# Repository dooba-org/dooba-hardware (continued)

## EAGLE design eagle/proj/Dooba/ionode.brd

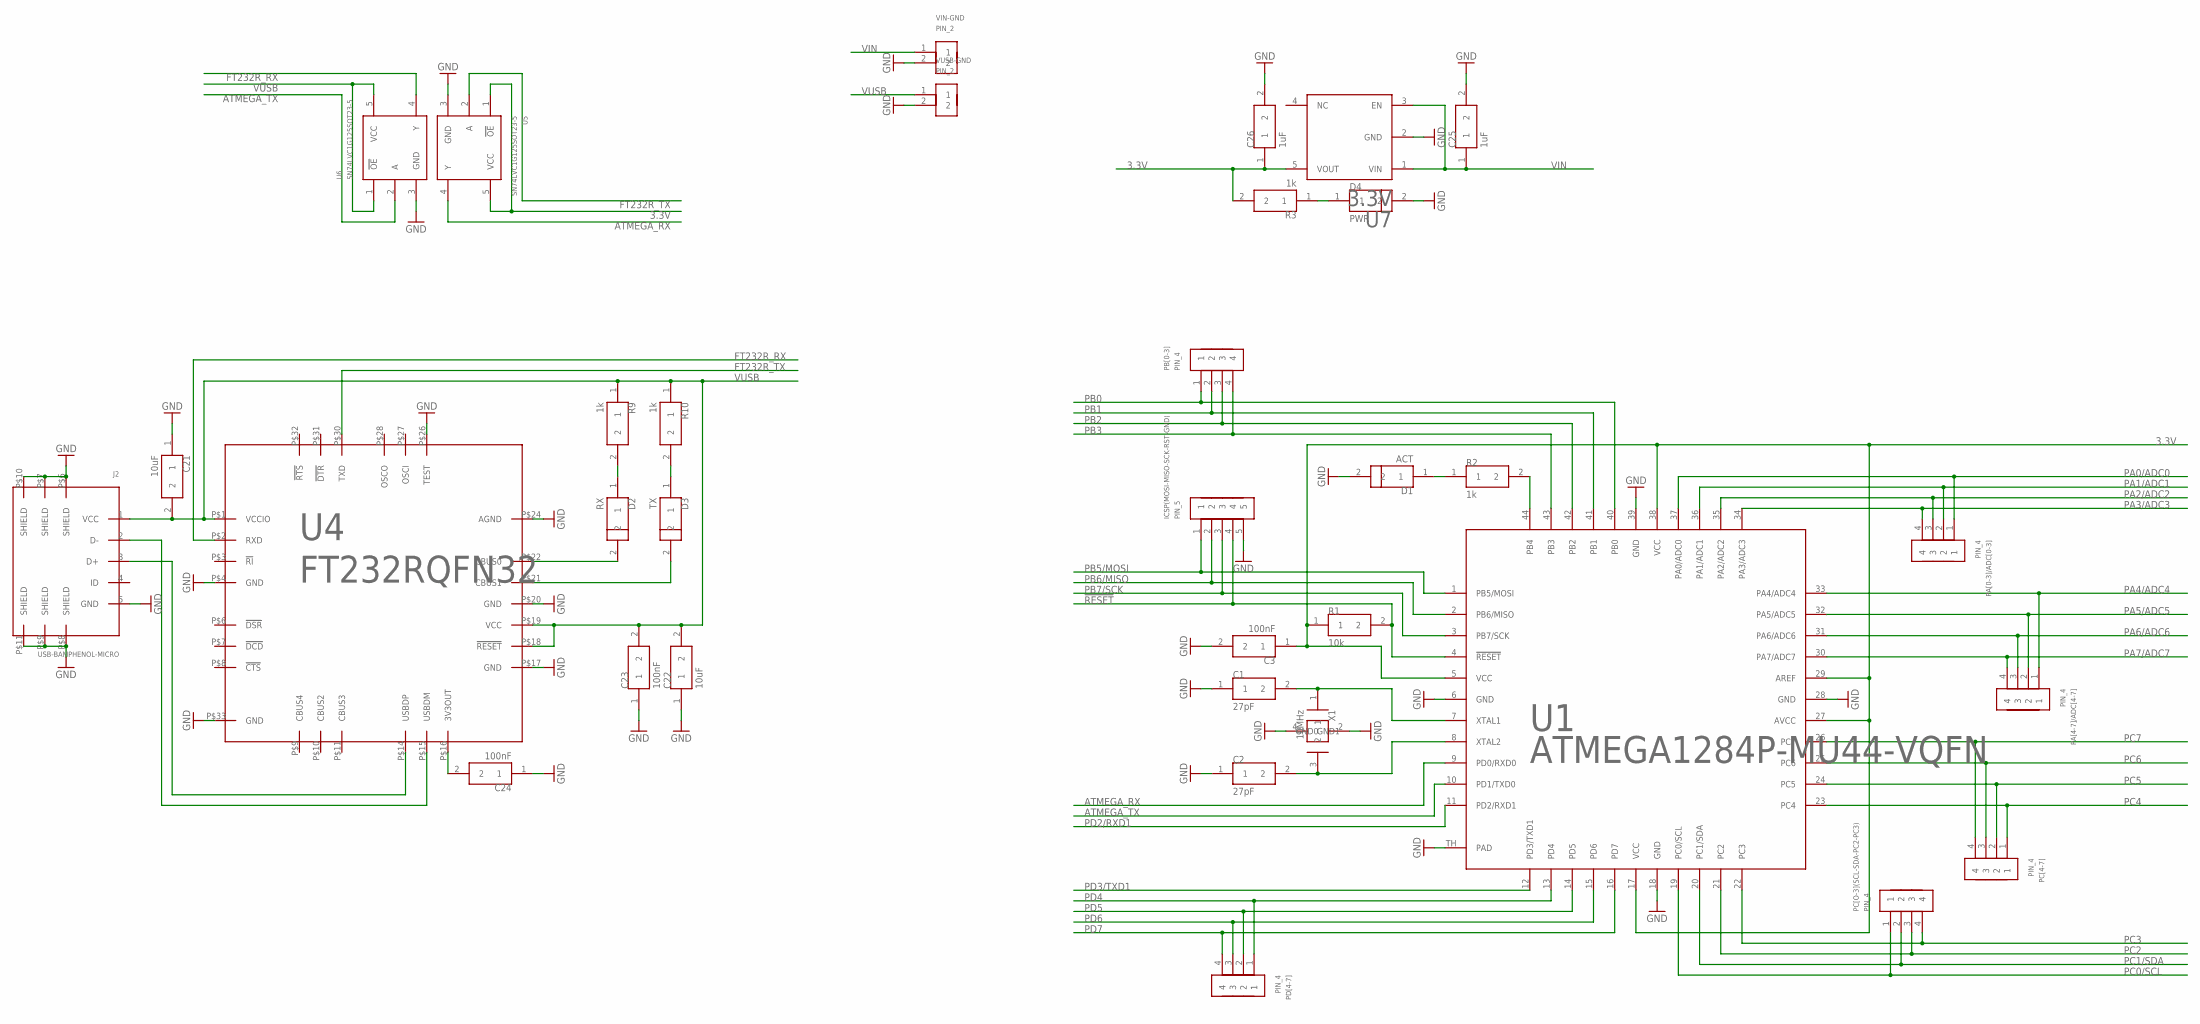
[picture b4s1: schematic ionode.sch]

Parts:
C1, C2: 27pF; 0805
C3, C23, C24: 100nF; 0805
C21, C22: 10uF; 0805
C25, C26: 1uF; 0805
D1: ACT; 0805
D2: RX; 0805
D3: TX; 0805
D4: PWR; 0805
ICSP(MOSI-MISO-SCK-RST-GND): PIN_5
J2: USB-BAMPHENOL-MICRO; AMPHENOL-USB-MICRO-B
PA[0-3]/ADC[0-3], PA[4-7]/ADC[4-7]: PIN_4
PB[0-3]: PIN_4
PC[4-7]: PIN_4
PC[O-3](SCL-SDA-PC2-PC3): PIN_4
PD[4-7]: PIN_4
R1: 10k; 0805
R2, R3, R9, R10: 1k; 0805
U1: ATMEGA1284P-MU44-VQFN; 44-VQFN
U4: FT232RQFN32; 32-VQFN
U5, U6: SN74LVC1G125SOT23-5; SOT23-5
U7: 3.3V; SOT23-5
VIN-GND: PIN_2
VUSB-GND: PIN_2
X1: 10MHz; XTAL_3225

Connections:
!RESET: ICSP(MOSI-MISO-SCK-RST-GND).4, R1.2, U1.4 (!RESET)
ATMEGA_RX: U1.9 (PD0/RXD0), U5.4 (Y)
ATMEGA_TX: U1.10 (PD1/TXD0), U6.2 (A)
FT232R_RX: U4.P$2 (RXD), U6.4 (Y)
FT232R_TX: U4.P$30 (TXD), U5.2 (A)
unnamed: C2.2, U1.8 (XTAL2), X1.3 (2)
unnamed: C1.2, U1.7 (XTAL1), X1.1
unnamed: D4.1, R3.1
unnamed: D1.1, R2.1
unnamed: R2.2, U1.44 (PB4)
unnamed: C24.2, U4.P$16 (3V3OUT)
unnamed: D2.2, U4.P$22 (CBUS0)
unnamed: D3.2, U4.P$21 (CBUS1)
unnamed: D2.1, R9.2
unnamed: D3.1, R10.2
unnamed: J2.2 (D-), U4.P$15 (USBDM)
unnamed: J2.3 (D+), U4.P$14 (USBDP)
PA0/ADC0: PA[0-3]/ADC[0-3].1, U1.37 (PA0/ADC0)
PA1/ADC1: PA[0-3]/ADC[0-3].2, U1.36 (PA1/ADC1)
PA2/ADC2: PA[0-3]/ADC[0-3].3, U1.35 (PA2/ADC2)
PA3/ADC3: PA[0-3]/ADC[0-3].4, U1.34 (PA3/ADC3)
PA4/ADC4: PA[4-7]/ADC[4-7].1, U1.33 (PA4/ADC4)
PA5/ADC5: PA[4-7]/ADC[4-7].2, U1.32 (PA5/ADC5)
PA6/ADC6: PA[4-7]/ADC[4-7].3, U1.31 (PA6/ADC6)
PA7/ADC7: PA[4-7]/ADC[4-7].4, U1.30 (PA7/ADC7)
PB0: PB[0-3].1, U1.40 (PB0)
PB1: PB[0-3].2, U1.41 (PB1)
PB2: PB[0-3].3, U1.42 (PB2)
PB3: PB[0-3].4, U1.43 (PB3)
PB5/MOSI: ICSP(MOSI-MISO-SCK-RST-GND).1, U1.1 (PB5/MOSI)
PB6/MISO: ICSP(MOSI-MISO-SCK-RST-GND).2, U1.2 (PB6/MISO)
PB7/SCK: ICSP(MOSI-MISO-SCK-RST-GND).3, U1.3 (PB7/SCK)
PC0/SCL: PC[O-3](SCL-SDA-PC2-PC3).1, U1.19 (PC0/SCL)
PC1/SDA: PC[O-3](SCL-SDA-PC2-PC3).2, U1.20 (PC1/SDA)
PC2: PC[O-3](SCL-SDA-PC2-PC3).3, U1.21 (PC2)
PC3: PC[O-3](SCL-SDA-PC2-PC3).4, U1.22 (PC3)
PC4: PC[4-7].1, U1.23 (PC4)
PC5: PC[4-7].2, U1.24 (PC5)
PC6: PC[4-7].3, U1.25 (PC6)
PC7: PC[4-7].4, U1.26 (PC7)
PD2/RXD1: U1.11 (PD2/RXD1)
PD3/TXD1: U1.12 (PD3/TXD1)
PD4: PD[4-7].1, U1.13 (PD4)
PD5: PD[4-7].2, U1.14 (PD5)
PD6: PD[4-7].3, U1.15 (PD6)
PD7: PD[4-7].4, U1.16 (PD7)
VIN: C25.1, U7.1 (VIN), U7.3 (EN), VIN-GND.1

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
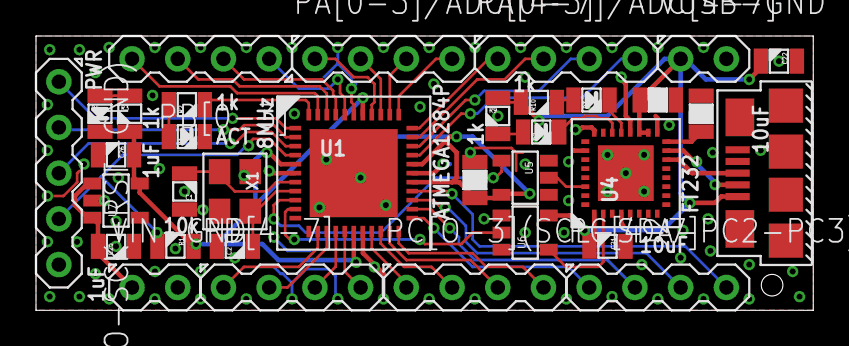
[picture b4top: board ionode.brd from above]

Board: 2 copper layers, 43.2 x 15.2 mm, 34 parts (0 on the bottom side), 48 nets.

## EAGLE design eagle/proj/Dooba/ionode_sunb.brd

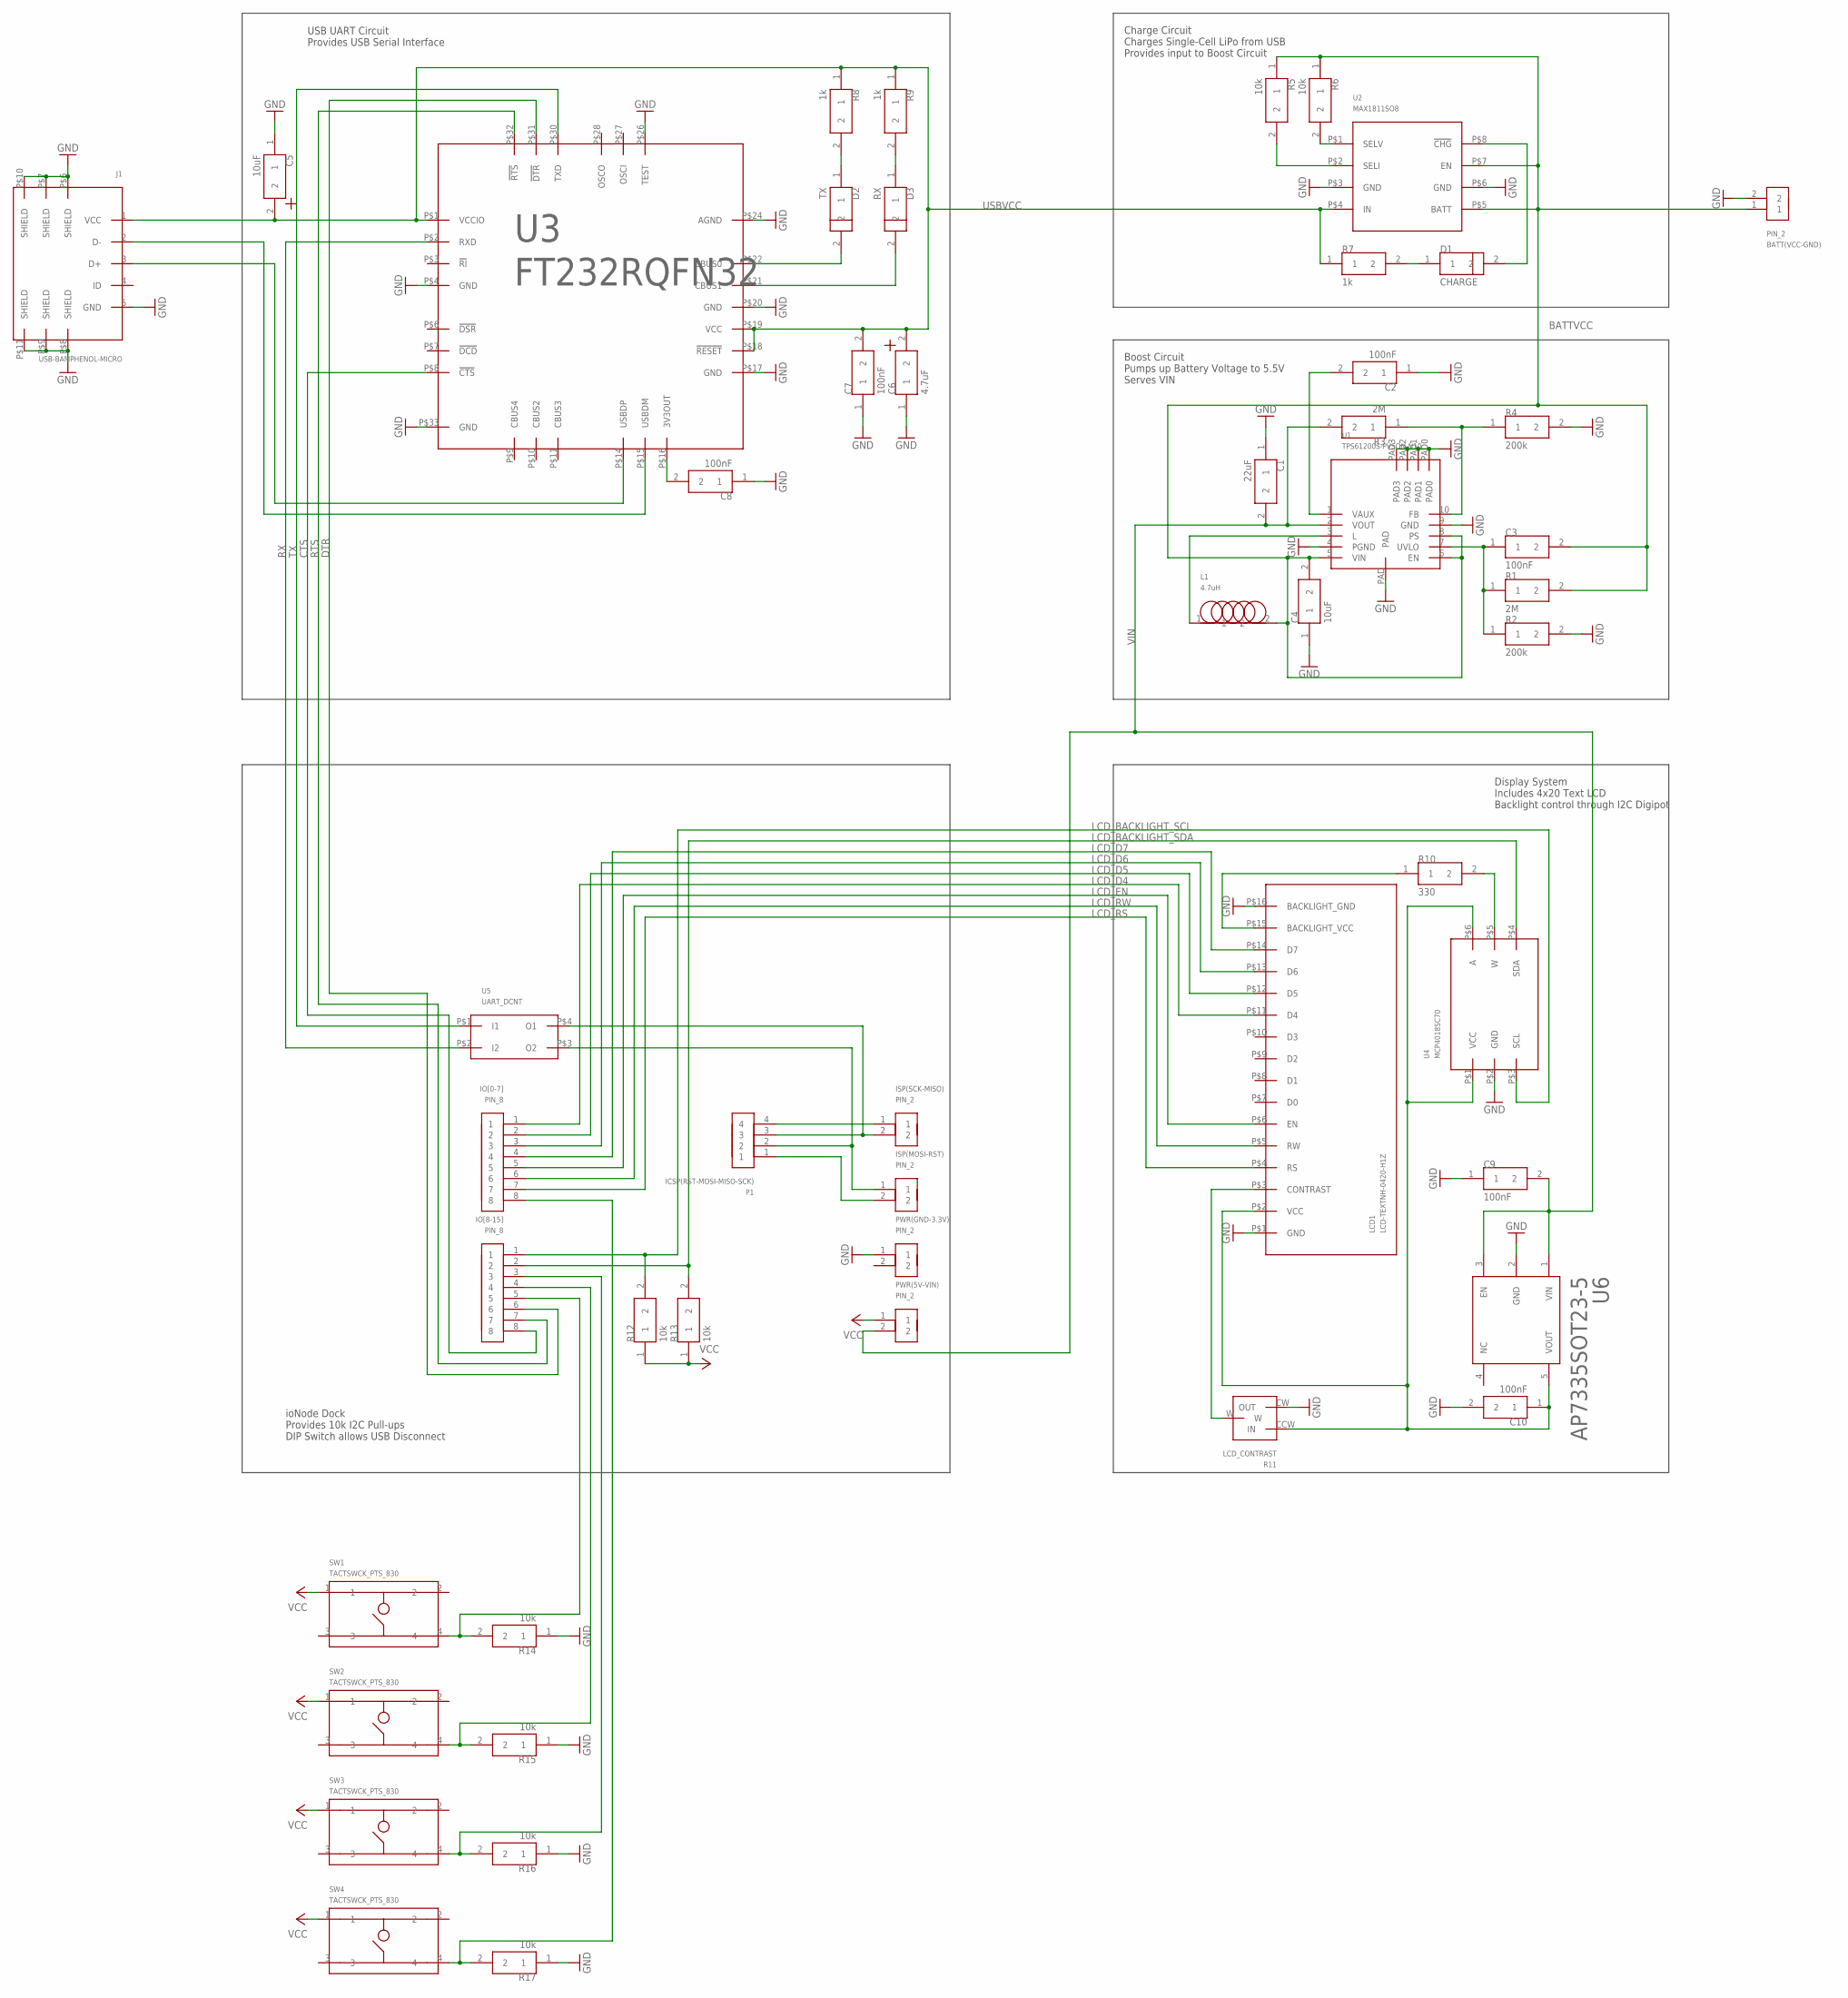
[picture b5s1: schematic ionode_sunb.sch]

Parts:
BATT(VCC-GND): PIN_2
C1: 22uF; 1206
C2, C3, C7, C8, C9, C10: 100nF; 0805
C4: 10uF; 0805
C5: 10uF; RADCAP_SMD_43
C6: 4.7uF; RADCAP_SMD_43
D1: CHARGE; 0805
D2: TX; 0805
D3: RX; 0805
IO[0-7], IO[8-15]: PIN_8
ISP(MOSI-RST): PIN_2
ISP(SCK-MISO): PIN_2
J1: USB-BAMPHENOL-MICRO; AMPHENOL-USB-MICRO-B
L1: 4.7uH; IND-SMD-3232
LCD1: LCD-TEXTNH-0420-H1Z; LCD-NH-0420-H1Z
P1: ICSP(RST-MOSI-MISO-SCK); PIN_4
PWR(5V-VIN): PIN_2
PWR(GND-3.3V): PIN_2
R1, R3: 2M; 0805
R2, R4: 200k; 0805
R5, R6, R12, R13, R14, R15, R16, R17: 10k; 0805
R7, R8, R9: 1k; 0805
R10: 330; 0805
R11: LCD_CONTRAST; TRIMPOT-BOURNS-3306F
SW1, SW2, SW3, SW4: TACTSWCK_PTS_830; TACTSW_CK_PTS_830
U1: TPS61200S-PVSON-N10; S-PVSON-N10
U2: MAX1811SO8; SO8
U3: FT232RQFN32; 32-VQFN
U4: MCP4018SC70; SC-70
U5: UART_DCNT; DIPSWITCH_2
U6: AP7335SOT23-5; SOT23-5

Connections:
BATTVCC: BATT(VCC-GND).1, C3.2, C4.2, L1.2, R1.2, R5.1, R6.1, U1.5 (VIN), U1.6 (EN), U1.8 (PS), U2.P$5 (BATT), U2.P$7 (EN)
CTS: IO[8-15].8, U3.P$8 (!CTS)
DTR: IO[8-15].6, U3.P$31 (!DTR)
GND: BATT(VCC-GND).2, C1.1, C2.1, C4.1, C5.1, C6.1, C7.1, C8.1, C9.1, C10.2, J1.5 (GND), J1.P$6 (SHIELD), J1.P$7 (SHIELD), J1.P$8 (SHIELD), J1.P$9 (SHIELD), J1.P$10 (SHIELD), J1.P$11 (SHIELD), LCD1.P$1 (GND), LCD1.P$16 (BACKLIGHT_GND), R2.2, R4.2, R11.CW (OUT), R14.1, R15.1, R16.1, R17.1, U1.4 (PGND), U1.9 (GND), U1.PAD, U1.PAD0, U1.PAD1, U1.PAD2, U1.PAD3, U2.P$3 (GND), U2.P$6 (GND), U3.P$4 (GND), U3.P$17 (GND), U3.P$20 (GND), U3.P$24 (AGND), U3.P$26 (TEST), U3.P$33 (GND), U4.P$2 (GND), U6.2 (GND)
LCDVCC: C10.1, LCD1.P$2 (VCC), R11.CCW (IN), U4.P$1 (VCC), U4.P$6 (A), U6.5 (VOUT)
LCD_BACKLIGHT_SCL: IO[8-15].1, R12.2, U4.P$3 (SCL)
LCD_BACKLIGHT_SDA: IO[8-15].2, R13.2, U4.P$4 (SDA)
LCD_D4: IO[0-7].1, LCD1.P$11 (D4)
LCD_D5: IO[0-7].2, LCD1.P$12 (D5)
LCD_D6: IO[0-7].3, LCD1.P$13 (D6)
LCD_D7: IO[0-7].4, LCD1.P$14 (D7)
LCD_EN: IO[0-7].5, LCD1.P$6 (EN)
LCD_RS: IO[0-7].7, LCD1.P$4 (RS)
LCD_RW: IO[0-7].6, LCD1.P$5 (RW)
unnamed: ISP(MOSI-RST).1, P1.2, U5.P$3 (O2)
unnamed: R6.2, U2.P$1 (SELV)
unnamed: R3.1, R4.1, U1.10 (FB)
unnamed: C2.2, U1.1 (VAUX)
unnamed: L1.1, U1.3 (L)
unnamed: C3.1, R1.1, R2.1, U1.7 (UVLO)
unnamed: R10.2, U4.P$5 (W)
unnamed: R5.2, U2.P$2 (SELI)
unnamed: LCD1.P$15 (BACKLIGHT_VCC), R10.1
unnamed: D1.2, U2.P$8 (!CHG)
unnamed: D1.1, R7.2
unnamed: LCD1.P$3 (CONTRAST), R11.W
unnamed: J1.2 (D-), U3.P$15 (USBDM)
unnamed: J1.3 (D+), U3.P$14 (USBDP)
unnamed: C8.2, U3.P$16 (3V3OUT)
unnamed: ISP(SCK-MISO).2, P1.3, U5.P$4 (O1)
unnamed: D2.2, U3.P$22 (CBUS0)
unnamed: D3.2, U3.P$21 (CBUS1)
unnamed: D2.1, R8.2
unnamed: D3.1, R9.2
unnamed: IO[8-15].5, R14.2, SW1.4
unnamed: IO[8-15].4, R15.2, SW2.4
unnamed: IO[8-15].3, R16.2, SW3.4
unnamed: IO[0-7].8, R17.2, SW4.4
unnamed: ISP(SCK-MISO).1, P1.4
unnamed: ISP(MOSI-RST).2, P1.1
RTS: IO[8-15].7, U3.P$32 (!RTS)
RX: U3.P$2 (RXD), U5.P$2 (I2)
TX: U3.P$30 (TXD), U5.P$1 (I1)
USBVCC: C5.2, C6.2, C7.2, J1.1 (VCC), R7.1, R8.1, R9.1, U2.P$4 (IN), U3.P$1 (VCCIO), U3.P$18 (!RESET), U3.P$19 (VCC)
VCC: PWR(5V-VIN).1, R12.1, R13.1, SW1.1, SW2.1, SW3.1, SW4.1
VIN: C1.2, C9.2, PWR(5V-VIN).2, R3.2, U1.2 (VOUT), U6.1 (VIN), U6.3 (EN)

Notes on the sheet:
Boost Circuit Pumps up Battery Voltage to 5.5V Serves VIN
Charge Circuit Charges Single-Cell LiPo from USB Provides input to Boost Circuit
USB UART Circuit Provides USB Serial Interface
Display System Includes 4x20 Text LCD Backlight control through I2C Digipot
ioNode Dock Provides 10k I2C Pull-ups DIP Switch allows USB Disconnect

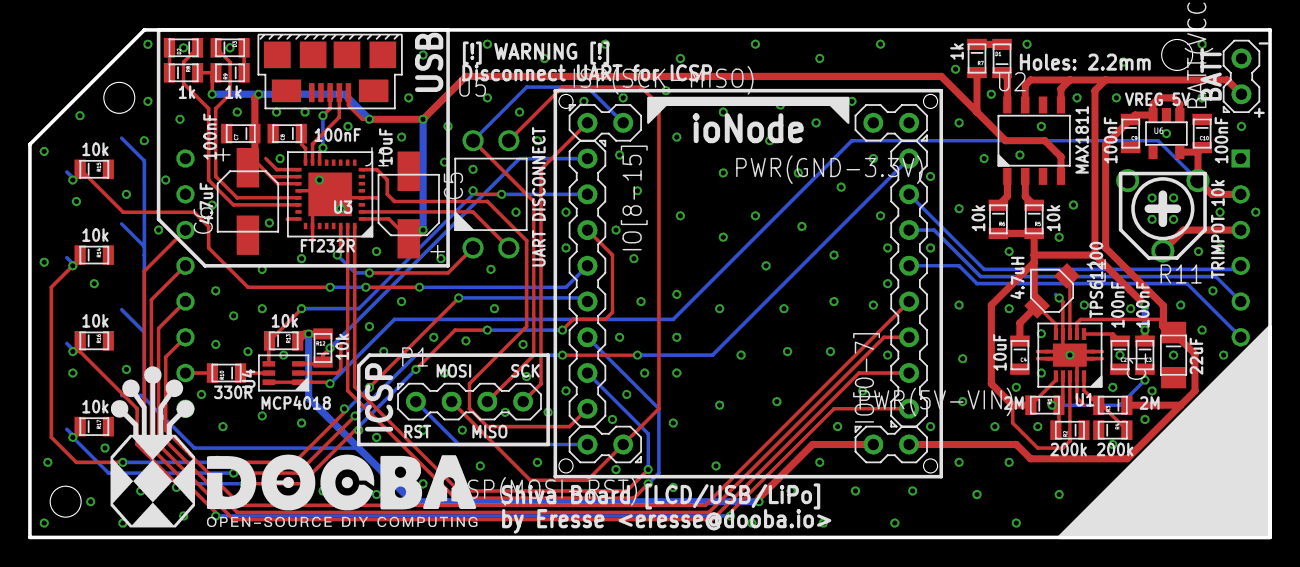
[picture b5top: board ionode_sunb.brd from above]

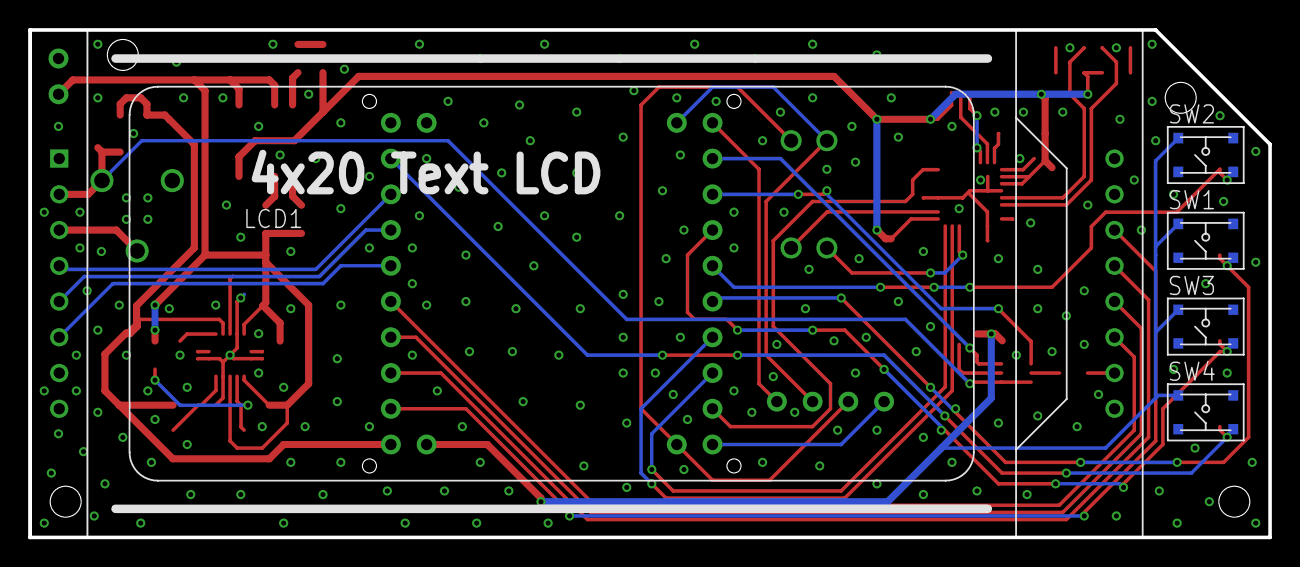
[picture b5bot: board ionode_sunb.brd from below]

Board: 2 copper layers, 88.1 x 36.1 mm, 51 parts (5 on the bottom side), 46 nets.

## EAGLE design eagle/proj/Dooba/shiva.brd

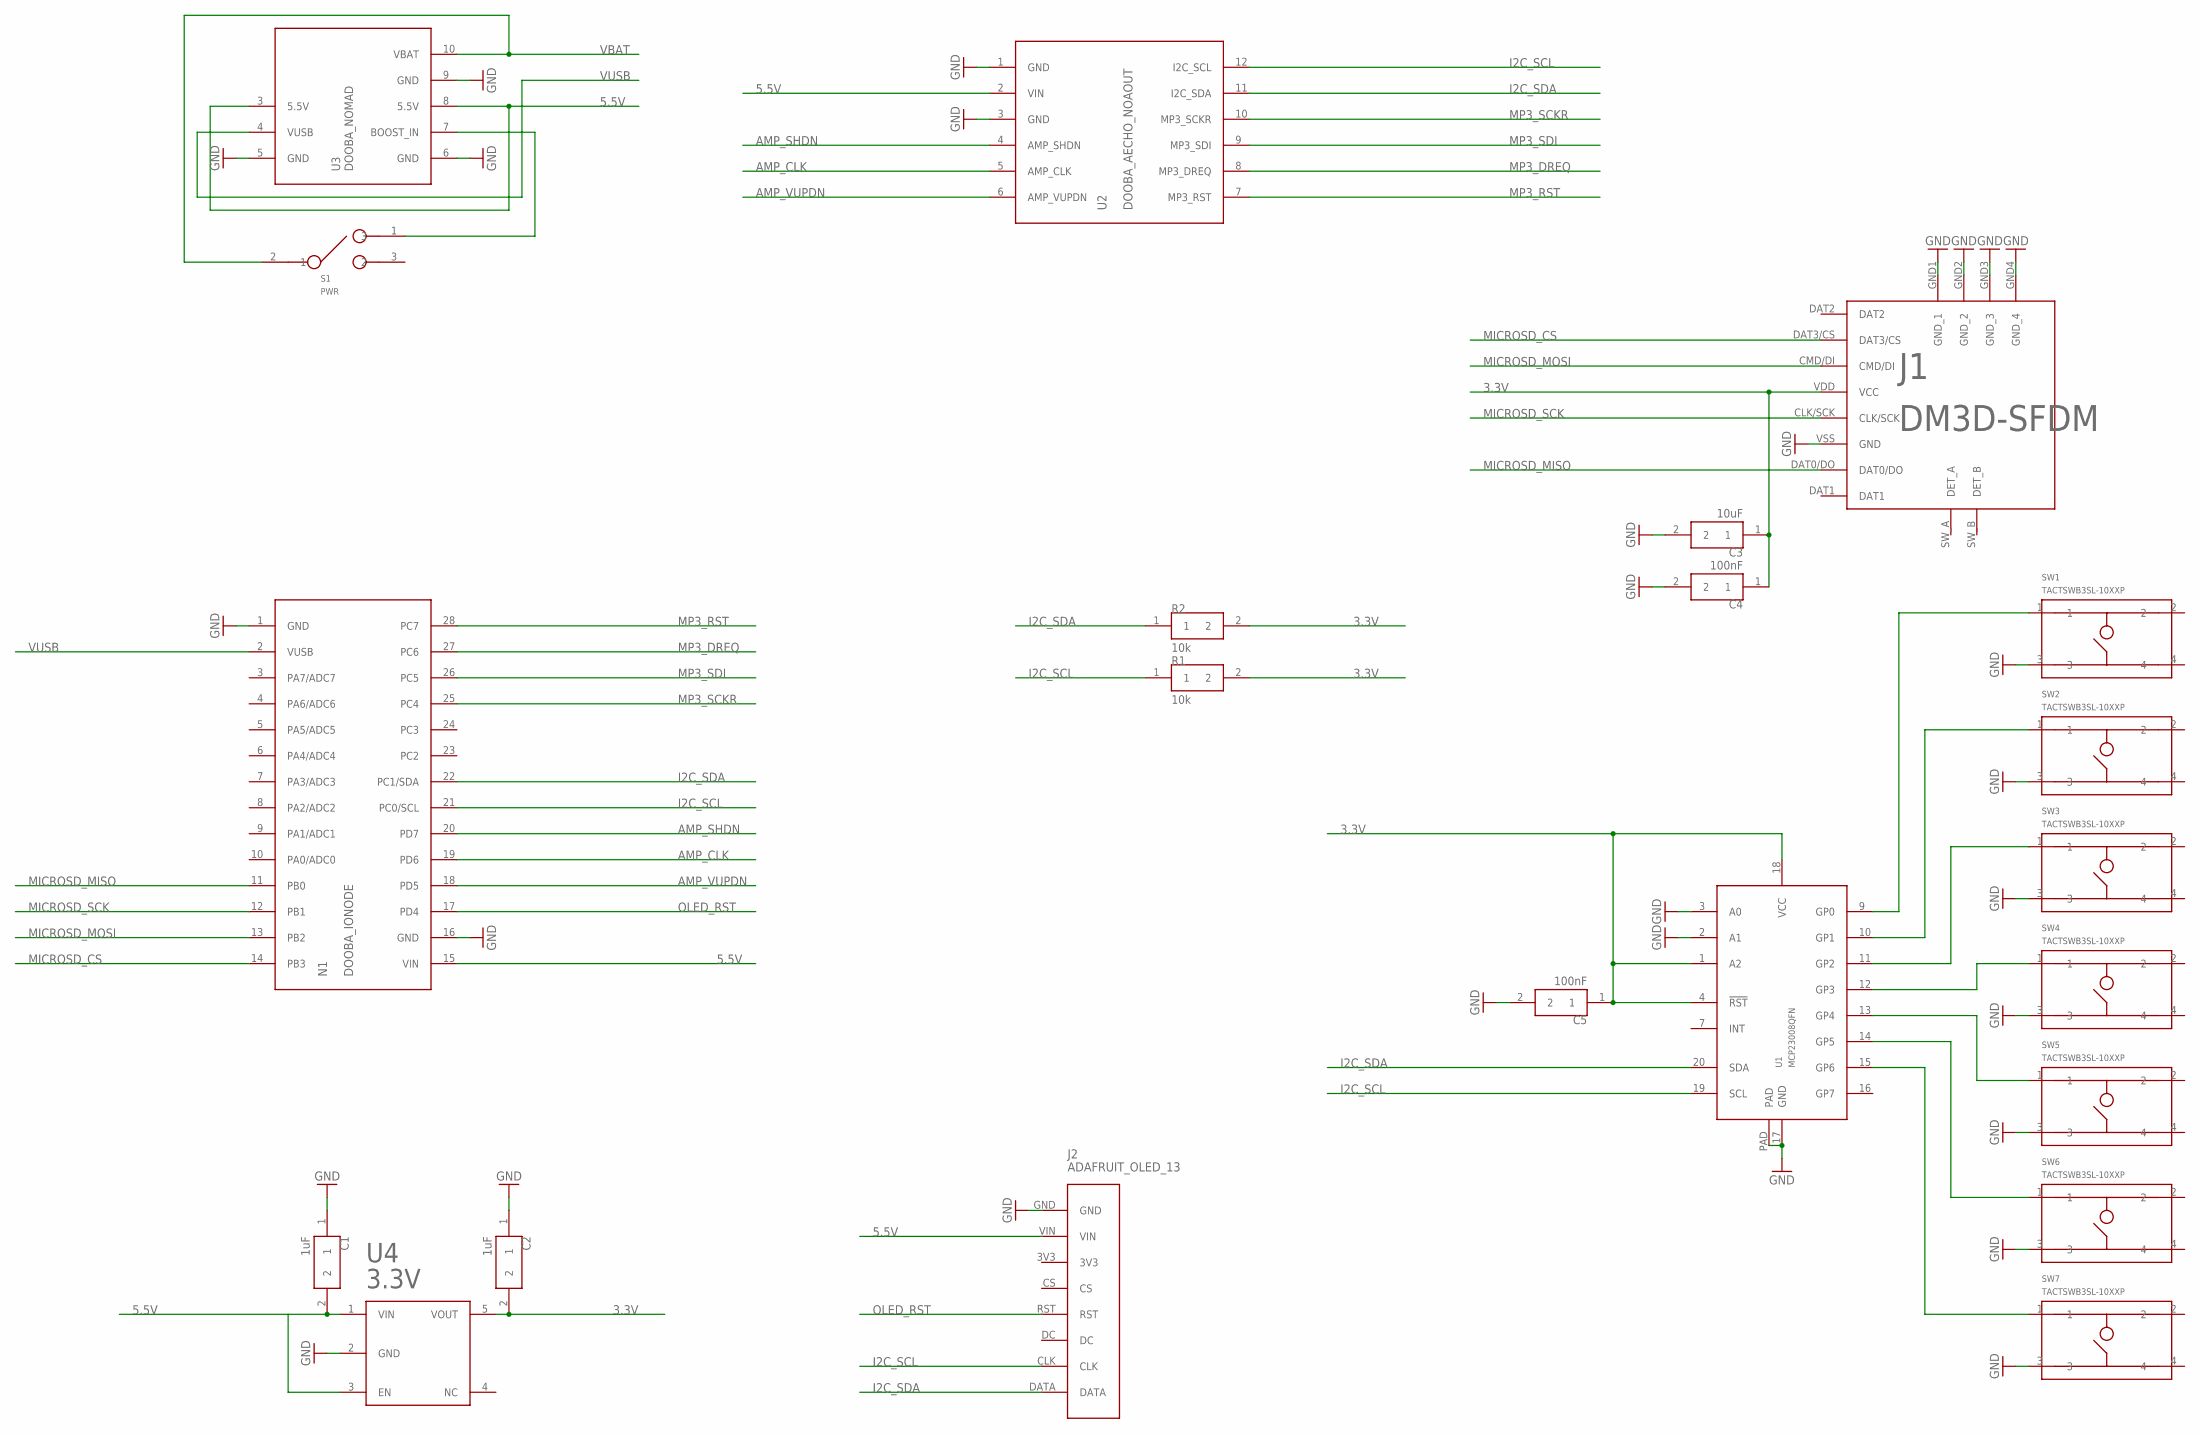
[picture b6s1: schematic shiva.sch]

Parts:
C1, C2: 1uF; 0805
C3: 10uF; 0805
C4, C5: 100nF; 0805
J1: DM3D-SFDM; DM3D-SF
J2: ADAFRUIT_OLED_13
N1: DOOBA_IONODE
R1, R2: 10k; 0805
S1: PWR; JS102011
SW1, SW2, SW3, SW4, SW5, SW6, SW7: TACTSWB3SL-10XXP; B3SL-10XXP
U1: MCP23008QFN; 20-VQFN
U2: DOOBA_AECHO_NOAOUT
U3: DOOBA_NOMAD
U4: 3.3V; SOT23-5

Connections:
3.3V: C2.2, C3.1, C4.1, C5.1, J1.VDD (VCC), R1.2, R2.2, U1.1 (A2), U1.4 (!RST), U1.18 (VCC), U4.5 (VOUT)
5.5V: C1.2, J2.VIN, N1.15 (VIN), U2.2 (VIN), U3.3 (5.5V), U3.8 (5.5V), U4.1 (VIN), U4.3 (EN)
AMP_CLK: N1.19 (PD6), U2.5 (AMP_CLK)
AMP_SHDN: N1.20 (PD7), U2.4 (AMP_SHDN)
AMP_VUPDN: N1.18 (PD5), U2.6 (AMP_VUPDN)
GND: C1.1, C2.1, C3.2, C4.2, C5.2, J1.GND1 (GND_1), J1.GND2 (GND_2), J1.GND3 (GND_3), J1.GND4 (GND_4), J1.VSS (GND), J2.GND, N1.1 (GND), N1.16 (GND), SW1.3, SW2.3, SW3.3, SW4.3, SW5.3, SW6.3, SW7.3, U1.2 (A1), U1.3 (A0), U1.17 (GND), U1.PAD, U2.1 (GND), U2.3 (GND), U3.5 (GND), U3.6 (GND), U3.9 (GND), U4.2 (GND)
I2C_SCL: J2.CLK, N1.21 (PC0/SCL), R1.1, U1.19 (SCL), U2.12 (I2C_SCL)
I2C_SDA: J2.DATA, N1.22 (PC1/SDA), R2.1, U1.20 (SDA), U2.11 (I2C_SDA)
MICROSD_CS: J1.DAT3/CS, N1.14 (PB3)
MICROSD_MISO: J1.DAT0/DO, N1.11 (PB0)
MICROSD_MOSI: J1.CMD/DI, N1.13 (PB2)
MICROSD_SCK: J1.CLK/SCK, N1.12 (PB1)
MP3_DREQ: N1.27 (PC6), U2.8 (MP3_DREQ)
MP3_RST: N1.28 (PC7), U2.7 (MP3_RST)
MP3_SCKR: N1.25 (PC4), U2.10 (MP3_SCKR)
MP3_SDI: N1.26 (PC5), U2.9 (MP3_SDI)
unnamed: SW1.1, U1.9 (GP0)
unnamed: SW2.1, U1.10 (GP1)
unnamed: SW3.1, U1.11 (GP2)
unnamed: SW4.1, U1.12 (GP3)
unnamed: SW5.1, U1.13 (GP4)
unnamed: SW6.1, U1.14 (GP5)
unnamed: SW7.1, U1.15 (GP6)
unnamed: S1.1 (3), U3.7 (BOOST_IN)
OLED_RST: J2.RST, N1.17 (PD4)
VBAT: S1.2 (1), U3.10 (VBAT)
VUSB: N1.2 (VUSB), U3.4 (VUSB)

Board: 2 copper layers, 22 parts (3 on the bottom side), 27 nets, no tracks yet.
